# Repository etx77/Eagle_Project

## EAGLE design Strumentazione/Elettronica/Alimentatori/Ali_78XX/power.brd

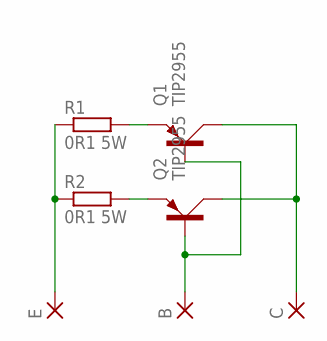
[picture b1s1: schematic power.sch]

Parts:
B: 3,81/1,4
C: 3,81/1,4
E: 3,81/1,4
Q1, Q2: TIP2955; TOP3AV
R1, R2: 0R1 5W; 0207/15

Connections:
unnamed: E.1, R1.1, R2.1
unnamed: Q1.E, R1.2
unnamed: Q2.E, R2.2
unnamed: C.1, Q1.C, Q2.C
unnamed: B.1, Q1.B, Q2.B

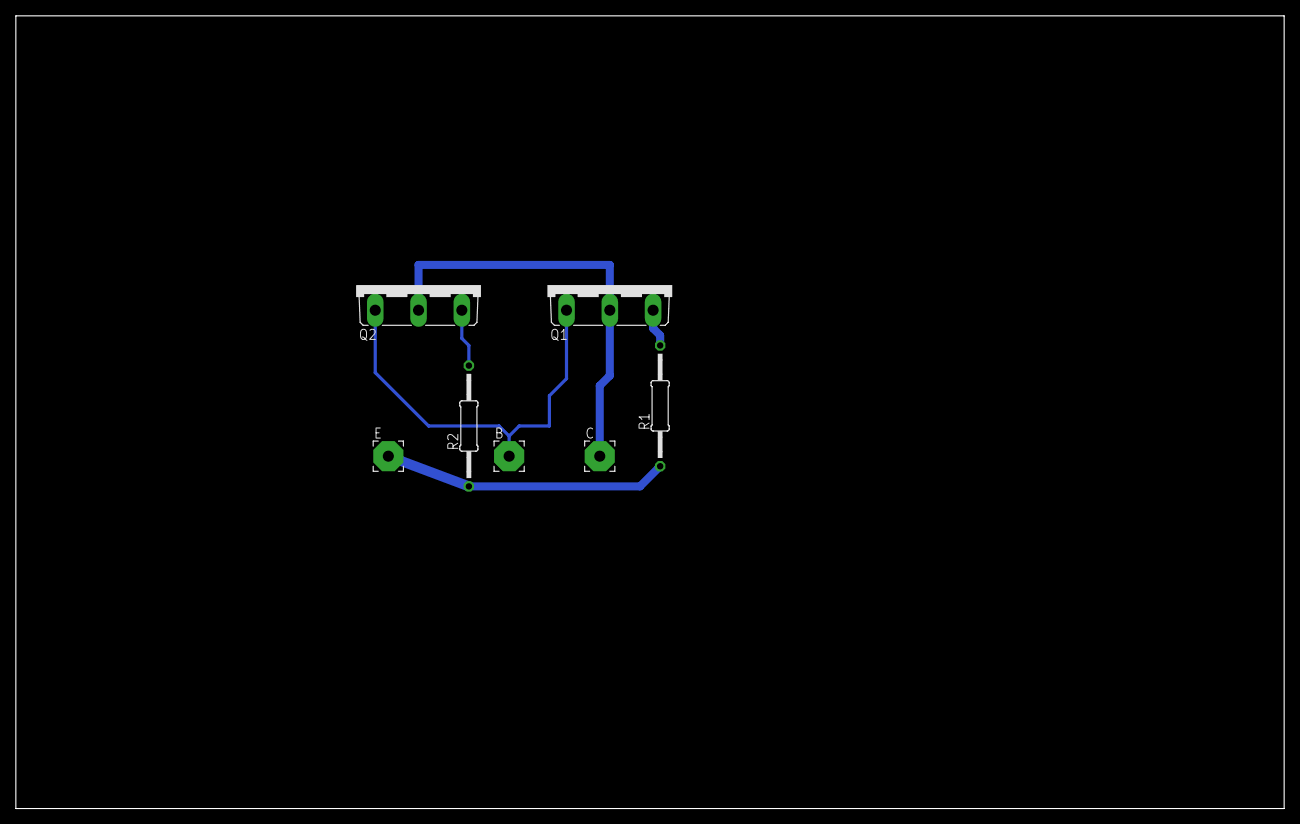
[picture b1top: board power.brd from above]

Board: 2 copper layers, 160.0 x 100.0 mm, 7 parts (0 on the bottom side), 5 nets.

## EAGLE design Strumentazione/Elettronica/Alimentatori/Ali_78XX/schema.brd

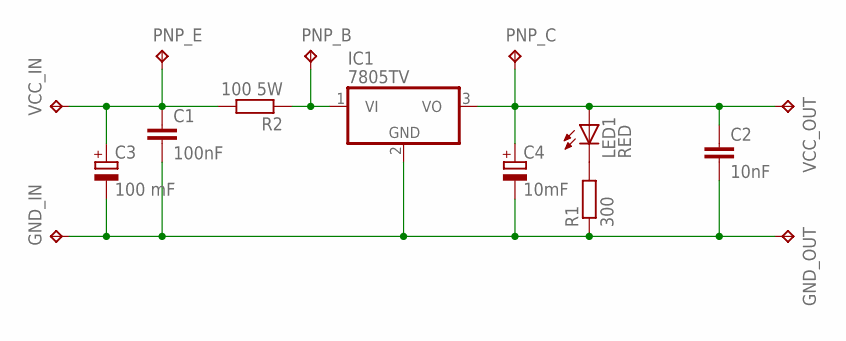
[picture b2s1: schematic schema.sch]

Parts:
C1: 100nF; C2.5-4
C2: 10nF; C2.5-4
C3: 100 mF; E5-13
C4: 10mF; E5-13
GND_IN: TPPAD1-20; P1-20
GND_OUT: TPPAD1-20; P1-20
IC1: 7805TV; TO220V
LED1: RED; LED3MM
PNP_B: TPPAD1-20Y; P1-20Y
PNP_C: TPPAD1-20Y; P1-20Y
PNP_E: TPPAD1-20Y; P1-20Y
R1: 300; 0204V
R2: 100 5W; 0204/7
VCC_IN: TPPAD1-20; P1-20
VCC_OUT: TPPAD1-20; P1-20

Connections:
unnamed: LED1.K (C), R1.2
unnamed: C1.1, C3.+, PNP_E.TP, R2.2, VCC_IN.TP
unnamed: C1.2, C2.2, C3.-, C4.-, GND_IN.TP, GND_OUT.TP, IC1.2 (GND), R1.1
unnamed: IC1.1 (VI), PNP_B.TP, R2.1
unnamed: C2.1, C4.+, IC1.3 (VO), LED1.A, PNP_C.TP, VCC_OUT.TP

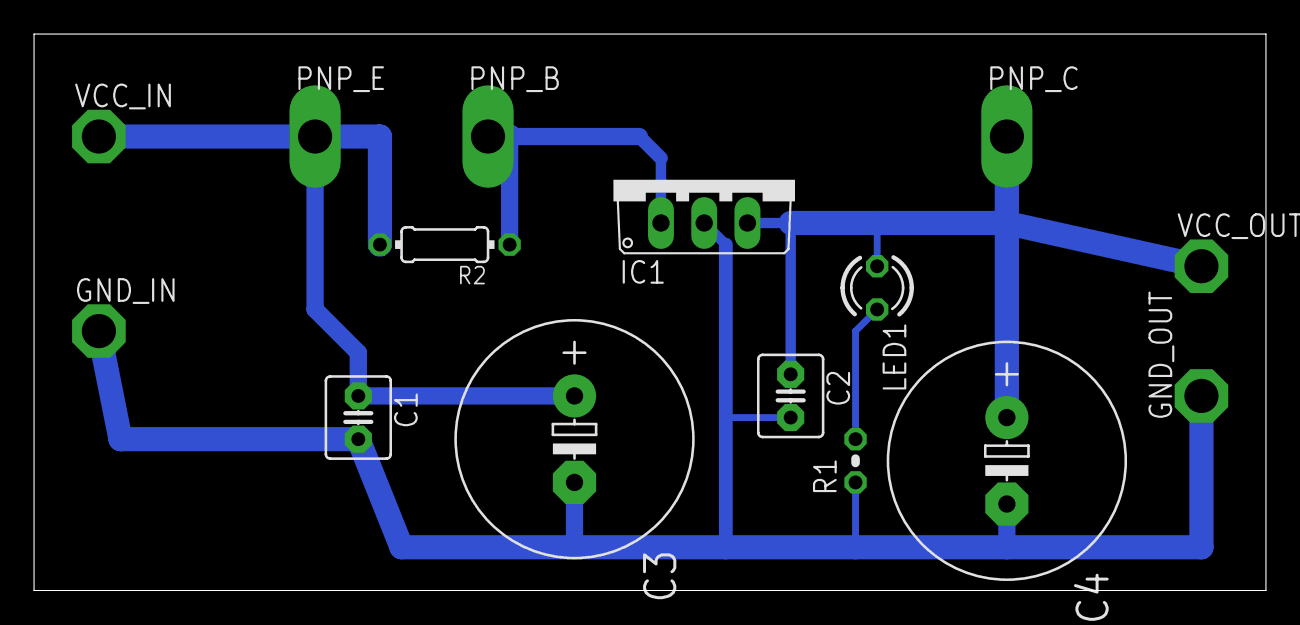
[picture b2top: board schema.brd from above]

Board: 2 copper layers, 72.4 x 32.7 mm, 15 parts (0 on the bottom side), 5 nets.

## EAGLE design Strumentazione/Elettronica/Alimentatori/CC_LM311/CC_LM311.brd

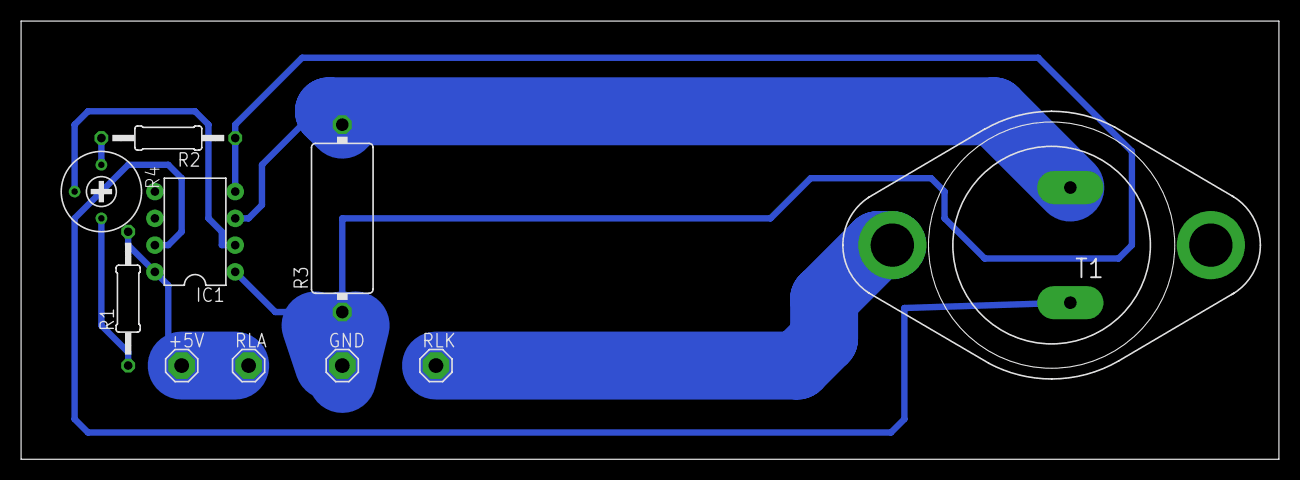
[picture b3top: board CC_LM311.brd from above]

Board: 2 copper layers, 119.4 x 41.6 mm, 10 parts (0 on the bottom side), 8 nets.

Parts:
+5V: SE14
GND: SE14
IC1: LM311N; DIL08
R1: 3K9; 0207/12
R2: 100; 0207/12
R3: 0R1 10W; V235/17
R4: 1K; RTRIM3339P
RLA: SE14
RLK: SE14
T1: 2N3055; TO3

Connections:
unnamed: +5V.MP, IC1.8, R1.2, RLA.MP
unnamed: R1.1, R4.3
unnamed: R2.2, R4.1
unnamed: GND.MP, IC1.1, IC1.4, R2.1, R3.1
unnamed: IC1.3, R3.2, T1.E
unnamed: IC1.7, T1.B
unnamed: RLK.MP, T1.C, T1.C/
unnamed: IC1.2, R4.2

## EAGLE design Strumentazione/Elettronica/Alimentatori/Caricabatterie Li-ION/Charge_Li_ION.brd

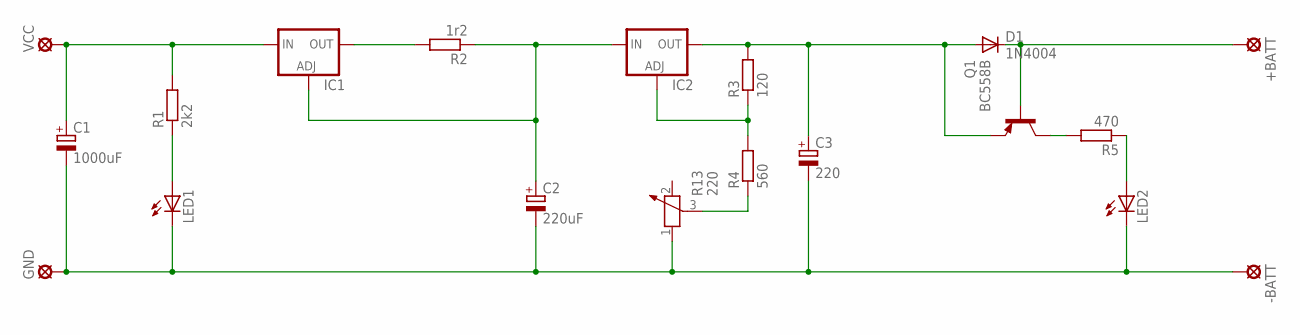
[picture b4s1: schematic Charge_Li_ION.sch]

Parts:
+BATT: LSP13
-BATT: LSP13
C1: 1000uF; E3,5-8
C2: 220uF; E3,5-8
C3: 220; E3,5-8
D1: 1N4004; DO41-10
GND: LSP13
IC1, IC2: LM317TS; 317TS
LED1, LED2: LED5MM
Q1: BC558B; TO92-EBC
R1: 2k2; 0207/7
R2: 1r2; 0207/7
R3: 120; 0207/7
R4: 560; 0207/7
R5: 470; 0207/7
R13: 220; PT-10
VCC: LSP13

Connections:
unnamed: LED1.A, R1.1
unnamed: C1.+, IC1.3 (IN), R1.2, VCC.MP
unnamed: IC1.2 (OUT), R2.2
unnamed: -BATT.MP, C1.-, C2.-, C3.-, GND.MP, LED1.K (C), LED2.K (C), R13.1
unnamed: C2.+, IC1.1 (ADJ), IC2.3 (IN), R2.1
unnamed: R4.1, R13.3
unnamed: IC2.1 (ADJ), R3.1, R4.2
unnamed: C3.+, D1.A, IC2.2 (OUT), Q1.E, R3.2
unnamed: +BATT.MP, D1.C, Q1.B
unnamed: Q1.C, R5.2
unnamed: LED2.A, R5.1

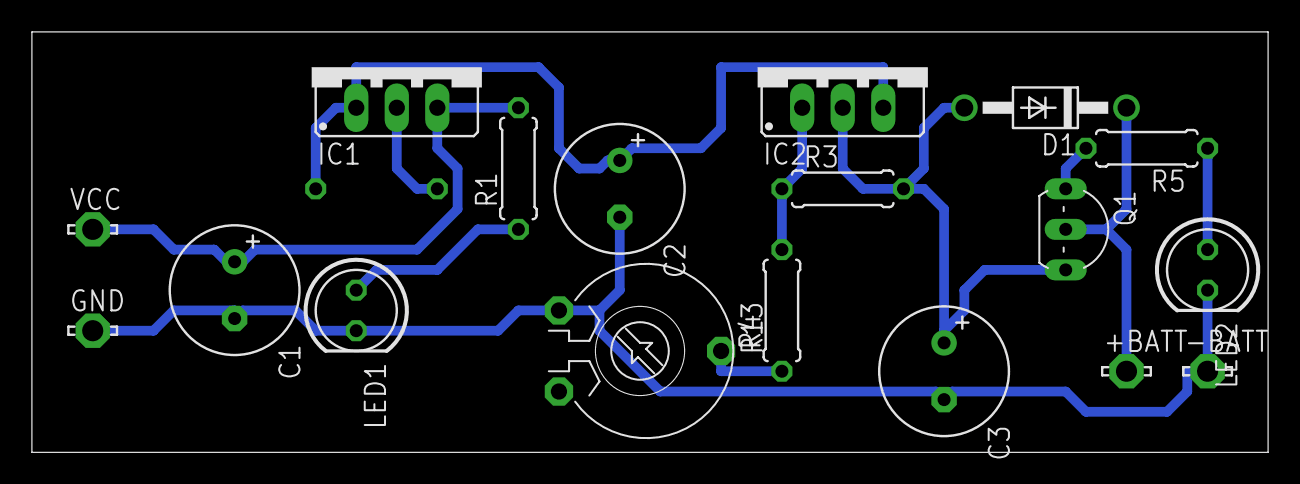
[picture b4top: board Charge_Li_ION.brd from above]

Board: 2 copper layers, 77.5 x 26.3 mm, 19 parts (1 on the bottom side), 11 nets.

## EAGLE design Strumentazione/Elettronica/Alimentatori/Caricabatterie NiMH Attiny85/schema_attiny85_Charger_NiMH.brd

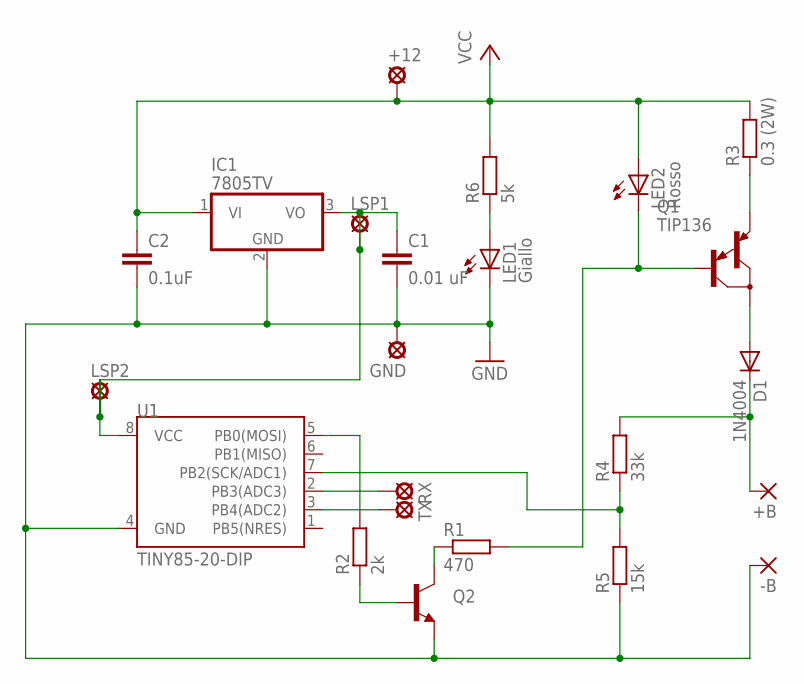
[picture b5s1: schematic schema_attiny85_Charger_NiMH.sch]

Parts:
+12: LSP10
+B: 1,6/0,9
-B: 1,6/0,9
C1: 0.01 uF; C050-025X075
C2: 0.1uF; C050-025X075
D1: 1N4004; DO41-10
GND: LSP10
IC1: 7805TV; TO220V
LED1: Giallo; LED5MM
LED2: Rosso; LED5MM
LSP1, LSP2: LSP10
Q1: TIP136; TO220
Q2: TRANSISTOR_NPNBC547; TO-92-AMMO
R1: 470; 0204/7
R2: 2k; 0204/7
R3: 0.3 (2W); 0204/7
R4: 33k; 0204/7
R5: 15k; 0204/7
R6: 5k; 0204/7
RX: LSP10
TX: LSP10
U1: TINY85-20-DIP; DIP08

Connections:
GND232: -B.1, C1.2, C2.2, GND.MP, IC1.2 (GND), LED1.K (C), Q2.3 (E), R5.1, U1.4 (GND)
unnamed: Q2.2 (B), R2.1
unnamed: C1.1, IC1.3 (VO), LSP1.MP, LSP2.MP, U1.8 (VCC)
unnamed: D1.A, Q1.2 (C)
unnamed: LED1.A, R6.1
unnamed: LED2.K (C), Q1.1 (B), R1.2
unnamed: Q1.3 (E), R3.1
unnamed: RX.MP, U1.2 (PB3(ADC3))
unnamed: +B.1, D1.C, R4.2
unnamed: R4.1, R5.2, U1.7 (PB2(SCK/ADC1))
unnamed: TX.MP, U1.3 (PB4(ADC2))
unnamed: Q2.1 (C), R1.1
unnamed: R2.2, U1.5 (PB0(MOSI))
VCC: +12.MP, C2.1, IC1.1 (VI), LED2.A, R3.2, R6.2

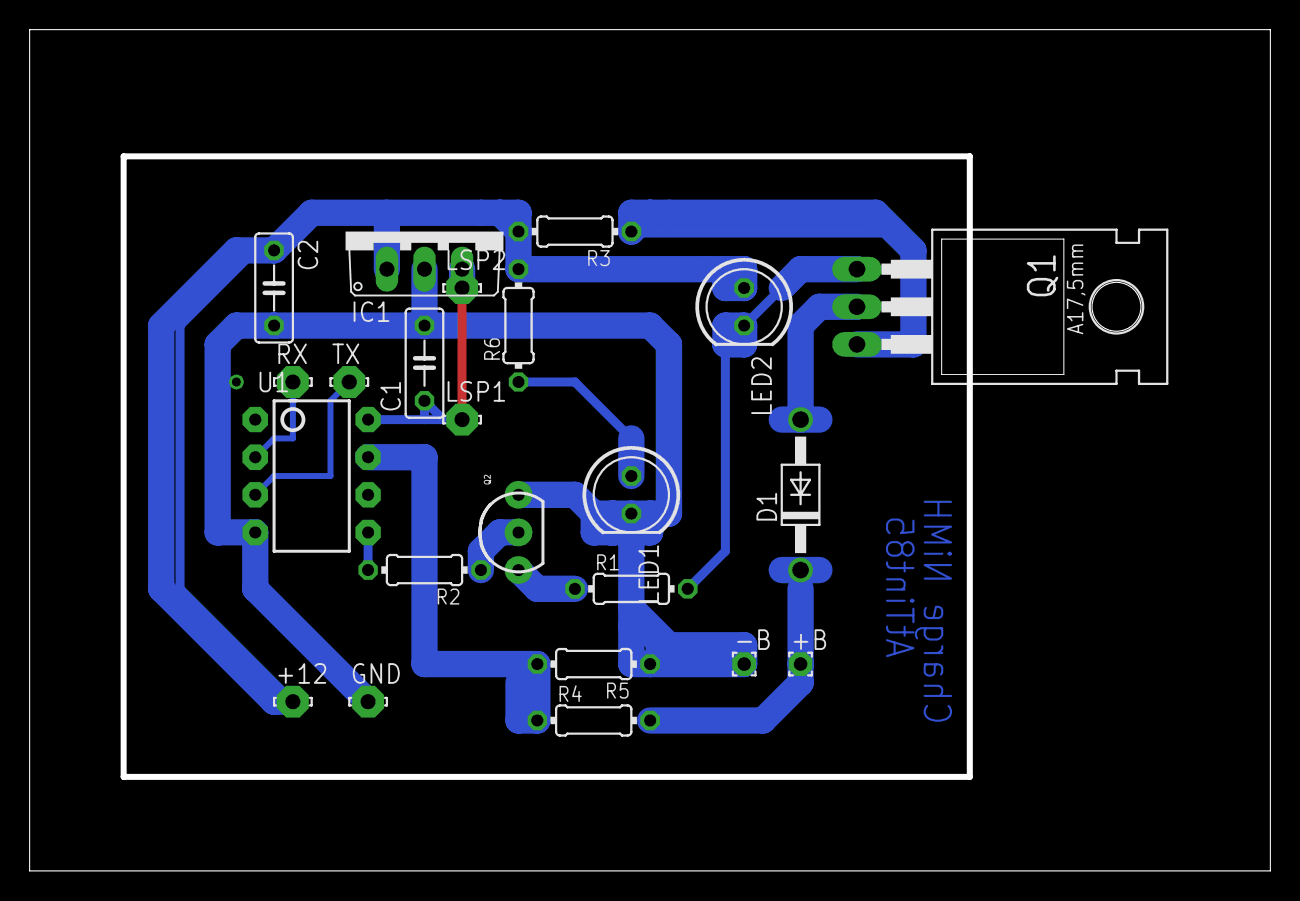
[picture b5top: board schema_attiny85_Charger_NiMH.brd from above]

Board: 2 copper layers, 83.8 x 56.8 mm, 23 parts (0 on the bottom side), 14 nets.

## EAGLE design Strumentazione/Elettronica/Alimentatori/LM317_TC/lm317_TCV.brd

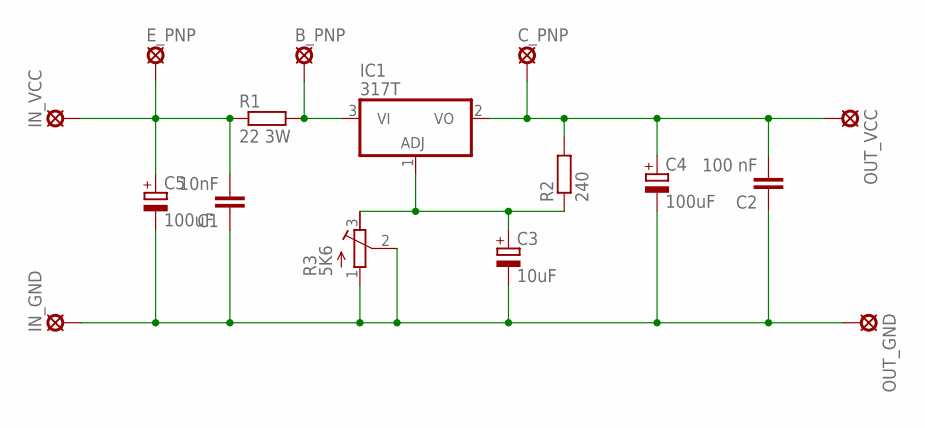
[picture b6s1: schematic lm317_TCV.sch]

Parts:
B_PNP: SE14
C1: 10nF; C7.5B3
C2: 100 nF; C7.5B3
C3: 10uF; E2,5-6E
C4, C5: 100uF; E2,5-6E
C_PNP: SE14
E_PNP: SE14
IC1: 317T; TO220H
IN_GND: SE14
IN_VCC: SE14
OUT_GND: SE14
OUT_VCC: SE14
R1: 22 3W; 0411/12
R2: 240; 0207/7
R3: 5K6; RTRIM3339P

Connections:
unnamed: C1.2, C5.+, E_PNP.MP, IN_VCC.MP, R1.1
unnamed: B_PNP.MP, IC1.3 (VI), R1.2
unnamed: C1.1, C2.1, C3.-, C4.-, C5.-, IN_GND.MP, OUT_GND.MP, R3.1 (A), R3.2 (S)
unnamed: C3.+, IC1.1 (ADJ), R2.1, R3.3 (E)
unnamed: C2.2, C4.+, C_PNP.MP, IC1.2 (VO), OUT_VCC.MP, R2.2

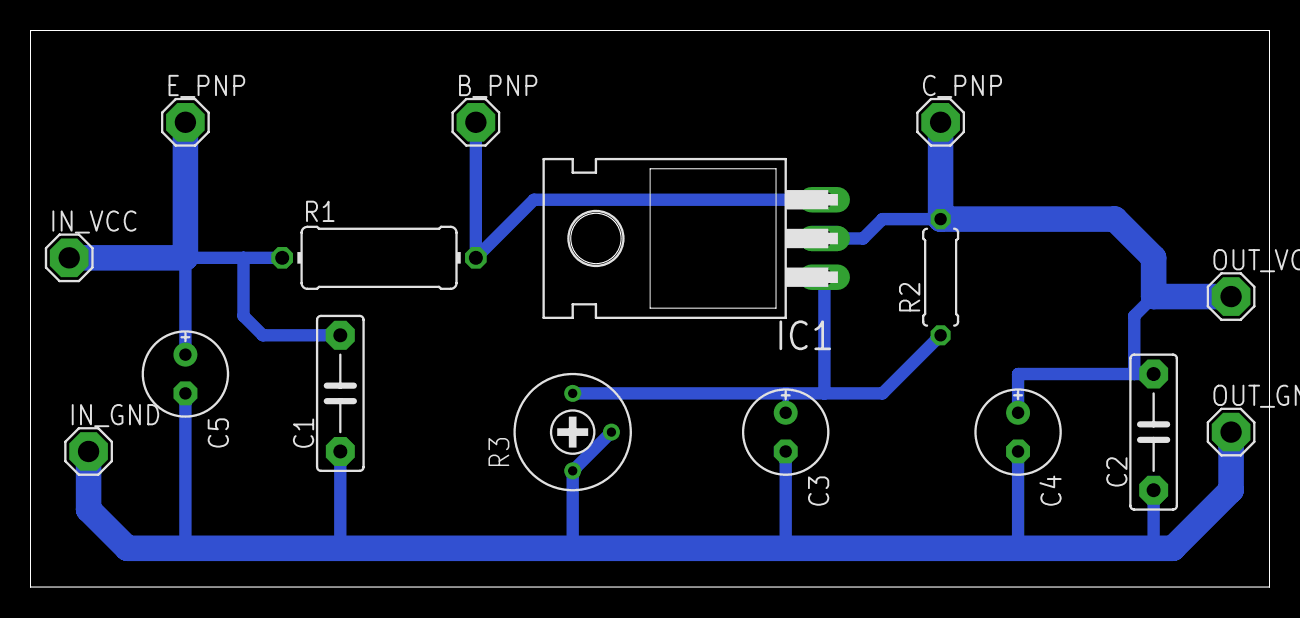
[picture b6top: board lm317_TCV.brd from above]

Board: 2 copper layers, 81.3 x 36.5 mm, 16 parts (0 on the bottom side), 5 nets.

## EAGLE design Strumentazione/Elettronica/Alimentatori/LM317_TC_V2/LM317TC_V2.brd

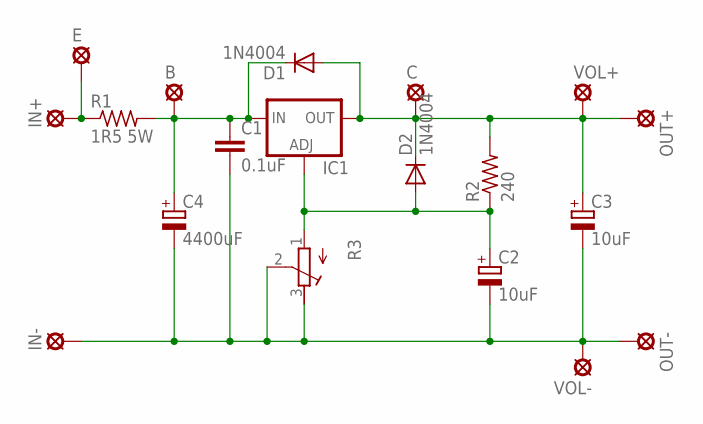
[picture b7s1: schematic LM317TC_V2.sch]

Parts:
B: LSP10
C: LSP10
C1: 0.1uF; C050-025X075
C2, C3: 10uF; E2,5-7
C4: 4400uF; E2,5-7
D1, D2: 1N4004; DO41-10
E: LSP10
IC1: LM317TS; 317TS
IN+: LSP10
IN-: LSP10
OUT+: LSP10
OUT-: LSP10
R1: 1R5 5W; 0207/15
R2: 240; 0207/10
R3: R-TRIMM3339P; RTRIM3339P
VOL+: LSP10
VOL-: LSP10

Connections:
unnamed: B.MP, C1.1, C4.+, D1.C, IC1.3 (IN), R1.2
unnamed: C.MP, C3.+, D1.A, D2.C, IC1.2 (OUT), OUT+.MP, R2.2, VOL+.MP
unnamed: C2.+, D2.A, IC1.1 (ADJ), R2.1, R3.1 (A)
unnamed: C1.2, C2.-, C3.-, C4.-, IN-.MP, OUT-.MP, R3.2 (S), R3.3 (E), VOL-.MP
unnamed: E.MP, IN+.MP, R1.1

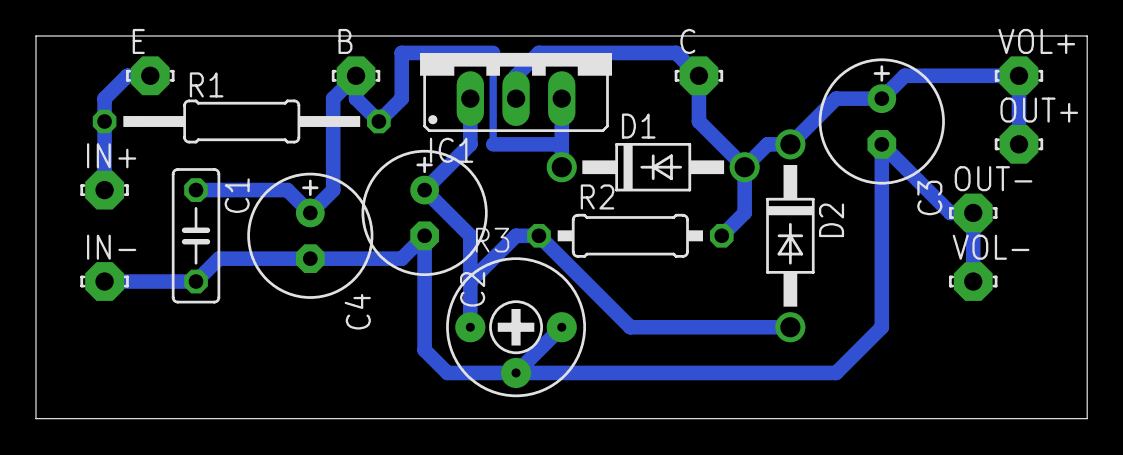
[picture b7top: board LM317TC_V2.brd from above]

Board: 2 copper layers, 58.4 x 21.3 mm, 19 parts (0 on the bottom side), 5 nets.

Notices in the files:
parts and their libraries:
SparkFun-DiscreteSemi: Licensing: Creative Commons ShareAlike 4.0 International - https://creativecommons.org/licenses/by-sa/4.0
